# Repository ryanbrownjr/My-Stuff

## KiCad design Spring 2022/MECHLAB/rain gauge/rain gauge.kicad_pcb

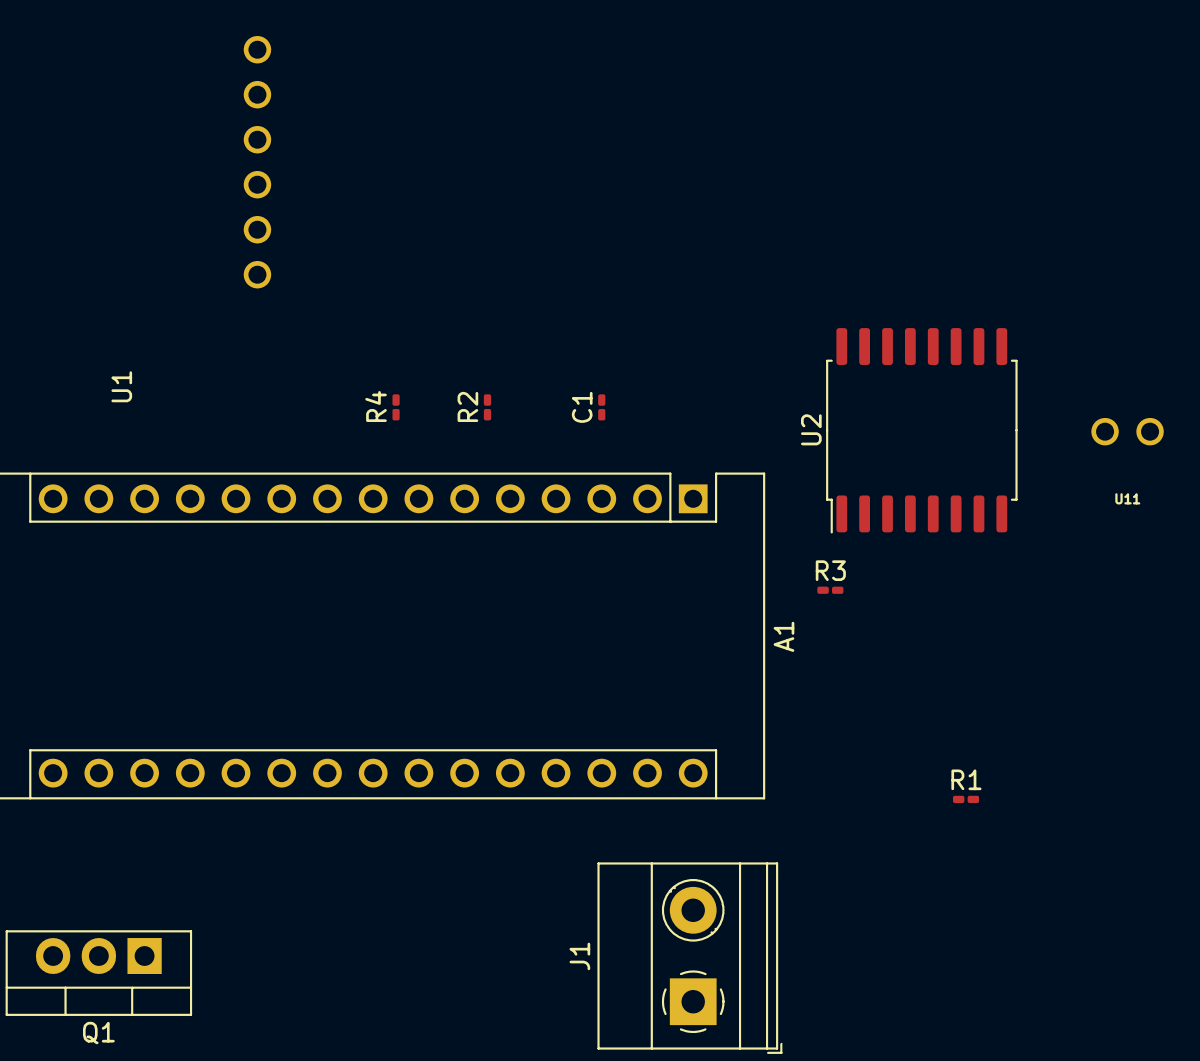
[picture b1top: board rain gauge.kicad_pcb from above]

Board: 2 copper layers, 11 parts (0 on the bottom side), 12 nets, no tracks yet.

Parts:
A1: Arduino_Nano_v3.x; Arduino_Nano
C1: C; C_0201_0603Metric_Pad0.64x0.40mm_HandSolder
J1: Screw_Terminal_01x02; TerminalBlock_Phoenix_MKDS-1,5-2-5.08_1x02_P5.08mm_Horizont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
Q1: IRF540N; TO-220-3_Vertical
R1, R3: 4.7K; R_0201_0603Metric_Pad0.64x0.40mm_HandSolder
R2: 10K; R_0201_0603Metric_Pad0.64x0.40mm_HandSolder
R4: 3.0M; R_0201_0603Metric_Pad0.64x0.40mm_HandSolder
U1: SDCARD; SDCard
U2: DS3231M; SOIC-16W_7.5x10.3mm_P1.27mm
U11: Battery

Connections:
GND: C1.2, R4.2, U1.1, U2.5, U2.6, U2.7, U2.8, U2.9, U2.10, U2.11, U2.12, U2.13
unnamed: A1.5, R3.2, U2.3
unnamed: A1.10, U1.5
unnamed: A1.14, U1.4
unnamed: A1.15, U1.2
unnamed: A1.16, U1.3
unnamed: A1.17, C1.1, R1.1, R2.1, R3.1, U1.6, U2.2
unnamed: A1.19, Q1.2, R4.1
unnamed: A1.23, R2.2, U2.15
unnamed: A1.24, R1.2, U2.16
unnamed: A1.27, J1.1, Q1.3
unnamed: J1.2, Q1.1

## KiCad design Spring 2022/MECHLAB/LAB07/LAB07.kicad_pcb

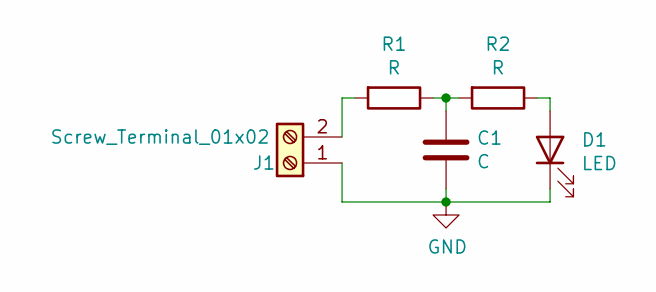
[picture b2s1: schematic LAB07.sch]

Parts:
C1: C; CP_Elec_8x10
D1: LED; LED_D3.0mm
J1: Screw_Terminal_01x02; TerminalBlock_Phoenix_MKDS-1,5-2-5.08_1x02_P5.08mm_Horizont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
R1, R2: R; R_1812_4532Metric

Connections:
GND: C1.2, D1.1 (K), J1.1
unnamed: C1.1, R1.1, R2.2
unnamed: D1.2 (A), R2.1
unnamed: J1.2, R1.2

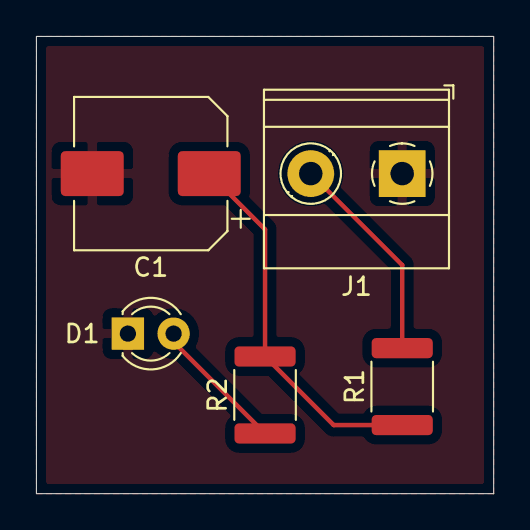
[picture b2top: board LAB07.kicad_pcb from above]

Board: 2 copper layers, 25.4 x 25.4 mm, 5 parts (0 on the bottom side), 4 nets.

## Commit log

2022-03-15 moving stuff
2022-03-15 Updates
    Lab stuff and arduino code
